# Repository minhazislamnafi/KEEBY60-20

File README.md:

# KEEBY60+20

A moduler 60% mechanical hot-swapble keyboard. With 20% numpad attachment, it will form a proper 80% keyboard.

# Specification

## KEEBY60
* Firmware: QMK
* Layout: Default 60% (main Keyboard)
* Socket: Hot-swapable Kailh Socket
* Switches: Cherry MX blue
* ARGB led: SK6812 mini-E
* MCU: Raspberry Pi RP2040 QFN-56
* USB hub IC: Fe1.1s SSOP-28
* USB IN: 2 type-C (One for USB+Power & another for only power)
* USB OUT: 1 6p magnetic connector & 2 type-c usb 2.0
        
     (2 USB 2.0 is only accessible when only 60% is used)
* Total keys: 63 ANSI layout
* Knob: EC11E rotary encoder (with push switch)
* Diaplay: SSD1306 0.91" I2C Oled 
* PCB: 2-layer (all components bottom mounted)
* Dimensions: pcb - 291* 116 mm (L * W)                                                                        
              case - 304* 130*45 mm  (L * W * H)

## KEEBY20
* firmware: QMK
* Layout: ISO 20% (numpad)
* Socket: Hot-swapable Kailh Socket
* Switches: Cherry MX blue
* ARGB led: SK6812 mini-E
* MCU: Raspberry Pi RP2040 QFN-56
* USB IN: 6p magnetic connector & 1 type-C

     (Both the 6p conn and type-C connector's data pin are connected)
* Total keys: 17 ANSI Numpad
* Knob: EC11E rotary encoder (with push switch)
* Diaplay: SSD1306 0.91" I2C Oled 
* PCB: 2-layer (all components bottom mounted)
* Dimensions: pcb - 81* 116 mm (L * W)                                                                         
              case - 95* 130*45 mm (L * W * H)

# Ask Why KEEBY60+20?

It's a freaking 80% moduler usb2.0 hub, mechanical hot-swappable programmable ARGB LED DIY 3D printed Keyboard with dual knob dual OLED display. wants to know more? It can be used as a single 60% ANSI with 2 USB 2.0 HUB or, a single 17-key numpad macropad or or or as said, a 6-pin magnetic-connected ISO 80% Keyboard. 

TL;DR - The KEEBY60+20 is an all-around very versatile keyboard that runs on open-source QMK firmware.

## Onshape Full assembly [Link](https://cad.onshape.com/documents/68f2d0f77eb15a6c900279e4/w/64c05305f9ae419810eaa342/e/0ee3c387e4a094a987680ffc?renderMode=0&uiState=6a25de67f901e47d9e05b22d)

## CAD Render

## Schematics

## PCB Render
My PC can't handle KiCad 10.0 now. so no render ;(
But I have some screenshots.

## FOLLOW THESE STEPS FOR BUILDING ##

**1. Spend some money $$ to buy the parts mentioned in [BOM](https://github.com/minhazislamnafi/KEEBY60-20/tree/main/PCB/production).**(2 separate BOM)

**2. Order the PCB for KEEBY60 and KEEBY20 using this [GERBER file](https://github.com/minhazislamnafi/KEEBY60-20/blob/main/PCB/production/keeby60/KEEBY_60_v1.1.zip) and [GERBER file](https://github.com/minhazislamnafi/KEEBY60-20/blob/main/PCB/production/keeby20/KEEBY_20_v1.1.zip).**

**3. Solder the SMD components of the PCB by hand ;) Or just order the PCBs with PCBA services, btw it will cost a lot.**

**4. Check with a multimeter: Is the MCU getting 3.3v or not? If not, diagnose by yourself :)**

**5. Place all the key switches.**

**6. Flash QMK firmware using USB connection ( I will add every step in details, once I have built IRL:)**

**7. 3D print the [Case](https://github.com/minhazislamnafi/KEEBY60-20/tree/main/CAD/CASE%203D%20file) .**

**8. Assemble your KEEBY60 and 20.**

**5. Test and enjoy more RGB= more FPS keyboard ( I will add every step in details, once I have built IRL:).**

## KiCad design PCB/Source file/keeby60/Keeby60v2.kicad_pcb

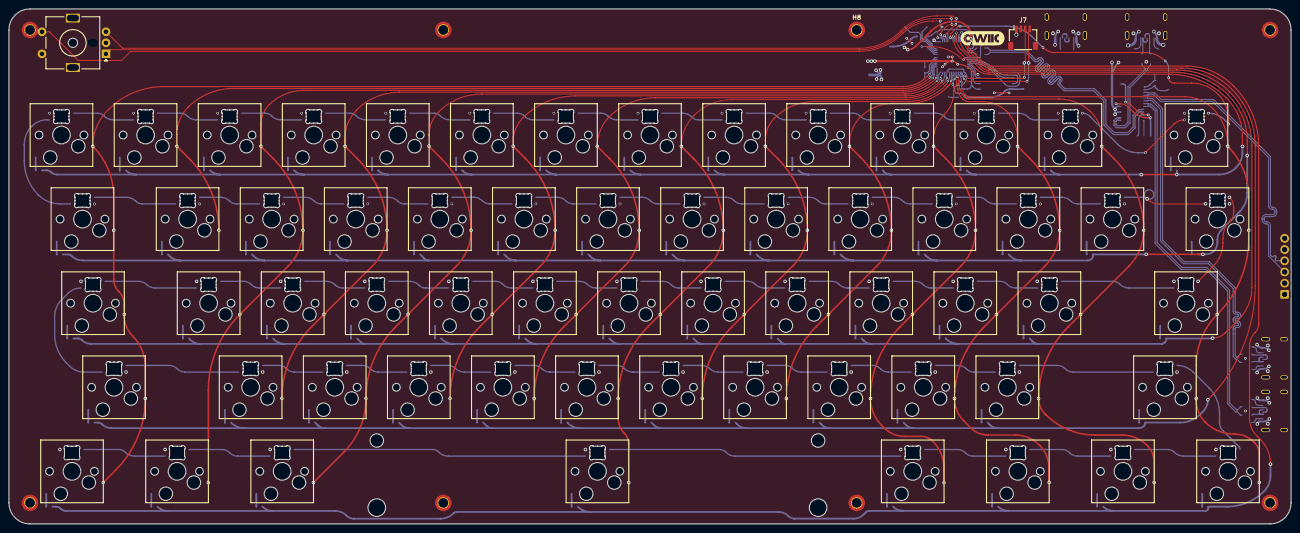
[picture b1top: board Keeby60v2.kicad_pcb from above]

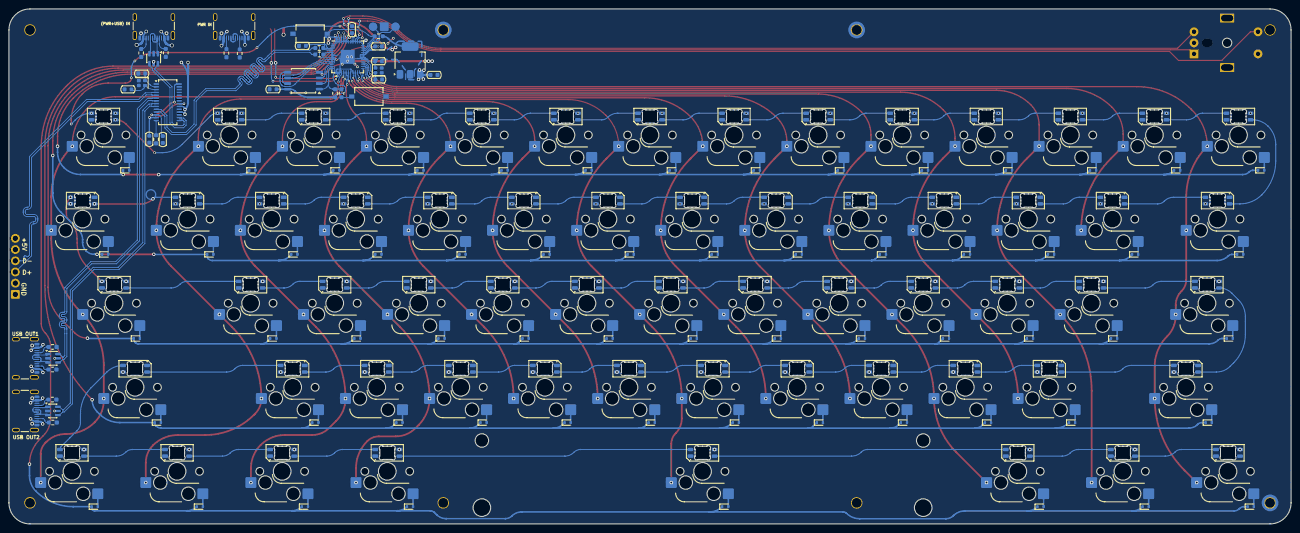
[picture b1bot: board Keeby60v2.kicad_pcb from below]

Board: 2 copper layers, 290.5 x 116.7 mm, 235 parts (163 on the bottom side), 195 nets.

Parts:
C7, C8, C14, C15: 10uF; C_0603_1608Metric
C9, C10: 27pF; C_0603_1608Metric
C11: 0.1uF; C_0603_1608Metric
C12: 100NF; C_0603_1608Metric
C13: 2.2uF; C_0603_1608Metric
C16, C17: 22pF; C_0603_1608Metric
D1, D2, D3, D4, D5, D6, D7, D8, D9, D10, D11, D12, D13, D14, D15, D16, D17, D18, D19, D20, D21, D22, D23, D24, D25, D26, D27, D28, D29, D30, D31, D32, D33, D34, D35, D36, D37, D38, D39, D40, D41, D42, D43, D44, D45, D46, D47, D48, D49, D50, D51, D52, D53, D54, D55, D56, D57, D58, D59, D60, D61: 1N4148WT; D_SOD-523
H1, H7, H8: MountingHole_Pad; MountingHole_2.2mm_M2_DIN965_Pad_TopBottom
H2, H3, H4, H5, H6: MountingHole_Pad; MountingHole_2.2mm_M2_DIN965_Pad_TopOnly
J1, J2, J3, J4: USB_C_Receptacle_USB2.0_16P; USB_C_Receptacle_GCT_USB4105-xx-A_16P_TopMnt_Horizontal
J5: 6P magnetic connecter; TerminalBlock_Xinya_XY308-2.54-6P_1x06_P2.54mm_Horizontal
J6: DEBUG PIN; TerminalBlock_Xinya_XY308-2.54-3P_1x03_P2.54mm_Horizontal
J7: Conn_01x05_Pin; JST_SH_SM04B-SRSS-TB_1x04-1MP_P1.00mm_Horizontal
L1, L2, L3, L4, L5, L6, L7, L8, L9, L10, L11, L12, L13, L14, L15, L16, L17, L18, L19, L20, L21, L22, L23, L24, L25, L26, L27, L28, L29, L30, L31, L32, L33, L34, L35, L36, L37, L38, L39, L40, L41, L42, L43, L44, L45, L46, L47, L48, L49, L50, L51, L52, L53, L54, L55, L56, L57, L58, L59, L60, L61: SK6812MINI-E; LED_SK6812MINI-E_3.2x2.8mm_P1.5mm_ReverseMount
R1, R2, R3, R4, R5, R6, R7, R8: 5.1K; R_0603_1608Metric_Pad0.98x0.95mm_HandSolder
R9, R10: 27R; R_0603_1608Metric_Pad0.98x0.95mm_HandSolder
R11: 1K; R_0603_1608Metric_Pad0.98x0.95mm_HandSolder
R12, R13: 10K; R_0603_1608Metric_Pad0.98x0.95mm_HandSolder
R14: 12K; R_0603_1608Metric_Pad0.98x0.95mm_HandSolder
SW1, SW2, SW3, SW4, SW5, SW6, SW7, SW8, SW9, SW10, SW11, SW12, SW13, SW16, SW17, SW18, SW19, SW20, SW21, SW22, SW23, SW24, SW25, SW26, SW27, SW30, SW31, SW32, SW33, SW34, SW35, SW36, SW37, SW38, SW39, SW40, SW43, SW44, SW45, SW46, SW47, SW48, SW49, SW50, SW51, SW52: SW_Push; SW_Hotswap_Kailh_MX_1.00u
SW14: SW_Push; SW_Hotswap_Kailh_MX_2.00u
SW15, SW28: SW_Push; SW_Hotswap_Kailh_MX_1.50u
SW29: SW_Push; SW_Hotswap_Kailh_MX_1.75u
SW41, SW42: SW_Push; SW_Hotswap_Kailh_MX_2.25u
SW53: SW_Push; SW_Hotswap_Kailh_MX_2.75u
SW54, SW55, SW56, SW58, SW59, SW60, SW61: SW_Push; SW_Hotswap_Kailh_MX_1.25u
SW57: SW_Push; SW_Hotswap_Kailh_MX_6.25u
SW62: RotaryEncoder_Switch_MP; RotaryEncoder_Alps_EC11E-Switch_Vertical_H20mm_MountingHoles
SW63, SW64: SW_Push; SW_Tactile_SPST_NO_Straight_CK_PTS636Sx25SMTRLFS
U4: RP2040; QFN-56-1EP_7x7mm_P0.4mm_EP3.2x3.2mm
U5: AMS1117-3.3; SOT-223-3_TabPin2
U6: W25Q128JVS; SOIC-8_5.3x5.3mm_P1.27mm
U7: FE1.1s; SSOP-28_3.9x9.9mm_P0.635mm
U8, U9, U10: USBLC6-2SC6; SOT-23-6
Y2, Y3: 12MHz; Crystal_SMD_2016-4Pin_2.0x1.6mm

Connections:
+5V: C7.1, J1.A4 (VBUS), J1.A9 (VBUS), J1.B4 (VBUS), J1.B9 (VBUS), J2.A4 (VBUS), J2.A9 (VBUS), J2.B4 (VBUS), J2.B9 (VBUS), J3.A4 (VBUS), J3.A9 (VBUS), J3.B4 (VBUS), J3.B9 (VBUS), J4.A4 (VBUS), J4.A9 (VBUS), J4.B4 (VBUS), J4.B9 (VBUS), J5.5, J5.6, J7.2, L1.3 (VDD), L2.3 (VDD), L3.3 (VDD), L4.3 (VDD), L5.3 (VDD), L6.3 (VDD), L7.3 (VDD), L8.3 (VDD), L9.3 (VDD), L10.3 (VDD), L11.3 (VDD), L12.3 (VDD), L13.3 (VDD), L14.3 (VDD), L15.3 (VDD), L16.3 (VDD), L17.3 (VDD), L18.3 (VDD), L19.3 (VDD), L20.3 (VDD), L21.3 (VDD), L22.3 (VDD), L23.3 (VDD), L24.3 (VDD), L25.3 (VDD), L26.3 (VDD), L27.3 (VDD), L28.3 (VDD), L29.3 (VDD), L30.3 (VDD), L31.3 (VDD), L32.3 (VDD), L33.3 (VDD), L34.3 (VDD), L35.3 (VDD), L36.3 (VDD), L37.3 (VDD), L38.3 (VDD), L39.3 (VDD), L40.3 (VDD), L41.3 (VDD), L42.3 (VDD), L43.3 (VDD), L44.3 (VDD), L45.3 (VDD), L46.3 (VDD), L47.3 (VDD), L48.3 (VDD), L49.3 (VDD), L50.3 (VDD), L51.3 (VDD), L52.3 (VDD), L53.3 (VDD), L54.3 (VDD), L55.3 (VDD), L56.3 (VDD), L57.3 (VDD), L58.3 (VDD), L59.3 (VDD), L60.3 (VDD), L61.3 (VDD), U5.3 (VI), U7.18 (VBUSM), U7.20 (VDD5), U8.5 (VBUS), U9.5 (VBUS), U10.5 (VBUS)
COL1: SW1.1, SW15.1, SW29.1, SW42.1, SW54.1, U4.18 (GPIO15)
COL2: SW2.1, SW16.1, U4.17 (GPIO14)
COL3: SW3.1, SW17.1, SW30.1, SW55.1, U4.16 (GPIO13)
COL4: SW4.1, SW18.1, SW31.1, SW43.1, U4.15 (GPIO12)
COL5: SW5.1, SW19.1, SW32.1, SW44.1, SW56.1, U4.14 (GPIO11)
COL6: SW6.1, SW20.1, SW33.1, SW45.1, U4.13 (GPIO10)
COL7: SW7.1, SW21.1, SW34.1, SW46.1, U4.12 (GPIO9)
COL8: SW8.1, SW22.1, SW35.1, SW47.1, SW57.1, U4.11 (GPIO8)
COL9: SW9.1, SW23.1, SW36.1, SW48.1, U4.9 (GPIO7)
COL10: SW10.1, SW24.1, SW37.1, SW49.1, U4.8 (GPIO6)
COL11: SW11.1, SW25.1, SW38.1, SW50.1, SW58.1, U4.7 (GPIO5)
COL12: SW12.1, SW26.1, SW39.1, SW51.1, SW59.1, U4.6 (GPIO4)
COL13: SW13.1, SW27.1, SW40.1, SW52.1, SW60.1, U4.5 (GPIO3)
COL14: SW14.1, SW28.1, SW41.1, SW53.1, SW61.1, U4.4 (GPIO2)
CS: R11.1, R12.2, U4.56 (~QSPI_SS), U6.1 (~CS)
DIN: L14.2 (DIN), U4.36 (GPIO24)
GND: C7.2, C8.2, C9.2, C10.1, C11.1, C12.1, C13.2, C14.1, C15.1, C16.1, C17.2, H1.1 (1_1), H2.1 (1_1), H3.1 (1_1), H5.1 (1_1), H6.1 (1_1), H7.1 (1_1), H8.1 (1_1), J1.A1 (GND), J1.A12 (GND), J1.B1 (GND), J1.B12 (GND), J1.SH (SHIELD), J2.A1 (GND), J2.A12 (GND), J2.B1 (GND), J2.B12 (GND), J2.SH (SHIELD), J3.A1 (GND), J3.A12 (GND), J3.B1 (GND), J3.B12 (GND), J3.SH (SHIELD), J4.A1 (GND), J4.A12 (GND), J4.B1 (GND), J4.B12 (GND), J4.SH (SHIELD), J5.1, J5.2, J6.2, J7.1, L1.1 (VSS), L2.1 (VSS), L3.1 (VSS), L4.1 (VSS), L5.1 (VSS), L6.1 (VSS), L7.1 (VSS), L8.1 (VSS), L9.1 (VSS), L10.1 (VSS), L11.1 (VSS), L12.1 (VSS), L13.1 (VSS), L14.1 (VSS), L15.1 (VSS), L16.1 (VSS), L17.1 (VSS), L18.1 (VSS), L19.1 (VSS), L20.1 (VSS), L21.1 (VSS), L22.1 (VSS), L23.1 (VSS), L24.1 (VSS), L25.1 (VSS), L26.1 (VSS), L27.1 (VSS), L28.1 (VSS), L29.1 (VSS), L30.1 (VSS), L31.1 (VSS), L32.1 (VSS), L33.1 (VSS), L34.1 (VSS), L35.1 (VSS), L36.1 (VSS), L37.1 (VSS), L38.1 (VSS), L39.1 (VSS), L40.1 (VSS), L41.1 (VSS), L42.1 (VSS), L43.1 (VSS), L44.1 (VSS), L45.1 (VSS), L46.1 (VSS), L47.1 (VSS), L48.1 (VSS), L49.1 (VSS), L50.1 (VSS), L51.1 (VSS), L52.1 (VSS), L53.1 (VSS), L54.1 (VSS), L55.1 (VSS), L56.1 (VSS), L57.1 (VSS), L58.1 (VSS), L59.1 (VSS), L60.1 (VSS), L61.1 (VSS), R1.2, R2.2, R3.2, R4.2, R5.2, R6.2, R7.2, R8.2, R14.1, SW62.C, SW62.MP, SW62.S2, SW63.2, SW64.1, U4.19 (TESTEN), U4.57 (GND), U5.1 (GND), U6.4 (GND), U7.1 (VSS), U7.27 (TESTJ/EESDA), U8.2 (GND), U9.2 (GND), U10.2 (GND), Y2.2 (G), Y2.3 (G), Y3.2 (G), Y3.3 (G)
MAG_D+: J5.3, U7.5 (DP4)
MAG_D-: J5.4, U7.4 (DM4)
MCU3.3V: C8.1, C11.2, R12.1, R13.2, U4.1 (IOVDD), U4.10 (IOVDD), U4.22 (IOVDD), U4.33 (IOVDD), U4.42 (IOVDD), U4.43 (ADC_AVDD), U4.44 (VREG_VIN), U4.48 (USB_VDD), U4.49 (IOVDD), U5.2 (VO), U6.8 (VCC)
MCU_D+: R9.1, U7.10 (DM1)
MCU_D-: R10.1, U7.11 (DP1)
unnamed: D1.2 (A), SW1.2
unnamed: D2.2 (A), SW2.2
unnamed: D3.2 (A), SW3.2
unnamed: D4.2 (A), SW4.2
unnamed: D5.2 (A), SW5.2
unnamed: D6.2 (A), SW6.2
unnamed: D7.2 (A), SW7.2
unnamed: D8.2 (A), SW8.2
unnamed: D9.2 (A), SW9.2
unnamed: D10.2 (A), SW10.2
unnamed: D11.2 (A), SW11.2
unnamed: D12.2 (A), SW12.2
unnamed: D13.2 (A), SW13.2
unnamed: D14.2 (A), SW14.2
unnamed: D15.2 (A), SW15.2
unnamed: D16.2 (A), SW16.2
unnamed: D17.2 (A), SW17.2
unnamed: D18.2 (A), SW18.2
unnamed: D19.2 (A), SW19.2
unnamed: D20.2 (A), SW20.2
unnamed: D21.2 (A), SW21.2
unnamed: D22.2 (A), SW22.2
unnamed: D23.2 (A), SW23.2
unnamed: D24.2 (A), SW24.2
unnamed: D25.2 (A), SW25.2
unnamed: D26.2 (A), SW26.2
unnamed: D27.2 (A), SW27.2
unnamed: D28.2 (A), SW28.2
unnamed: D29.2 (A), SW29.2
unnamed: D30.2 (A), SW30.2
unnamed: D31.2 (A), SW31.2
unnamed: D32.2 (A), SW32.2
unnamed: D33.2 (A), SW33.2
unnamed: D34.2 (A), SW34.2
unnamed: D35.2 (A), SW35.2
unnamed: D36.2 (A), SW36.2
unnamed: D37.2 (A), SW37.2
unnamed: D38.2 (A), SW38.2
unnamed: D39.2 (A), SW39.2
unnamed: D40.2 (A), SW40.2
unnamed: D41.2 (A), SW41.2
unnamed: D42.2 (A), SW42.2
unnamed: D43.2 (A), SW43.2
unnamed: D44.2 (A), SW44.2
unnamed: D45.2 (A), SW45.2
unnamed: D46.2 (A), SW46.2
unnamed: D47.2 (A), SW47.2
unnamed: D48.2 (A), SW48.2
unnamed: D49.2 (A), SW49.2
unnamed: D50.2 (A), SW50.2
unnamed: D51.2 (A), SW51.2
unnamed: D52.2 (A), SW52.2
unnamed: D53.2 (A), SW53.2
unnamed: D54.2 (A), SW54.2
unnamed: D55.2 (A), SW55.2
unnamed: D56.2 (A), SW56.2
unnamed: D57.2 (A), SW57.2
unnamed: D58.2 (A), SW58.2
unnamed: D59.2 (A), SW59.2
unnamed: D60.2 (A), SW60.2
unnamed: D61.2 (A), SW61.2
unnamed: J1.A5 (CC1), R5.1
unnamed: J1.B5 (CC2), R6.1
unnamed: J1.A6 (D+), J1.B6 (D+), U8.3 (I/O2)
unnamed: J1.A7 (D-), J1.B7 (D-), U8.1 (I/O1)
unnamed: J2.A5 (CC1), R1.1
unnamed: J2.B5 (CC2), R2.1
unnamed: J2.A6 (D+), J2.B6 (D+), U9.3 (I/O2)
unnamed: J2.A7 (D-), J2.B7 (D-), U9.1 (I/O1)
unnamed: J3.A5 (CC1), R3.1
unnamed: J3.B5 (CC2), R4.1
unnamed: J3.A6 (D+), J3.B6 (D+), U10.3 (I/O2)
unnamed: J3.A7 (D-), J3.B7 (D-), U10.1 (I/O1)
unnamed: J4.A5 (CC1), R7.1
unnamed: J4.B5 (CC2), R8.1
unnamed: J4.A6 (D+), J4.B6 (D+)
unnamed: J4.A7 (D-), J4.B7 (D-)
unnamed: L1.2 (DIN), L2.4 (DOUT)
unnamed: L1.4 (DOUT), L15.2 (DIN)
unnamed: L2.2 (DIN), L3.4 (DOUT)
unnamed: L3.2 (DIN), L4.4 (DOUT)
unnamed: L4.2 (DIN), L5.4 (DOUT)
unnamed: L5.2 (DIN), L6.4 (DOUT)
unnamed: L6.2 (DIN), L7.4 (DOUT)
unnamed: L7.2 (DIN), L8.4 (DOUT)
unnamed: L8.2 (DIN), L9.4 (DOUT)
unnamed: L10.2 (DIN), L11.4 (DOUT)
unnamed: L9.2 (DIN), L10.4 (DOUT)
unnamed: L11.2 (DIN), L12.4 (DOUT)
unnamed: L12.2 (DIN), L13.4 (DOUT)
unnamed: L13.2 (DIN), L14.4 (DOUT)
unnamed: L15.4 (DOUT), L16.2 (DIN)
unnamed: L16.4 (DOUT), L17.2 (DIN)
unnamed: L17.4 (DOUT), L18.2 (DIN)
unnamed: L18.4 (DOUT), L19.2 (DIN)
unnamed: L19.4 (DOUT), L20.2 (DIN)
unnamed: L20.4 (DOUT), L21.2 (DIN)
unnamed: L21.4 (DOUT), L22.2 (DIN)
unnamed: L22.4 (DOUT), L23.2 (DIN)
unnamed: L23.4 (DOUT), L24.2 (DIN)
unnamed: L24.4 (DOUT), L25.2 (DIN)
unnamed: L25.4 (DOUT), L26.2 (DIN)
unnamed: L26.4 (DOUT), L27.2 (DIN)
unnamed: L27.4 (DOUT), L28.2 (DIN)
unnamed: L28.4 (DOUT), L41.2 (DIN)
unnamed: L29.2 (DIN), L30.4 (DOUT)
unnamed: L29.4 (DOUT), L42.2 (DIN)
unnamed: L30.2 (DIN), L31.4 (DOUT)
unnamed: L31.2 (DIN), L32.4 (DOUT)
unnamed: L32.2 (DIN), L33.4 (DOUT)
unnamed: L33.2 (DIN), L34.4 (DOUT)
unnamed: L34.2 (DIN), L35.4 (DOUT)
unnamed: L35.2 (DIN), L36.4 (DOUT)
unnamed: L36.2 (DIN), L37.4 (DOUT)
unnamed: L37.2 (DIN), L38.4 (DOUT)
unnamed: L38.2 (DIN), L39.4 (DOUT)
unnamed: L39.2 (DIN), L40.4 (DOUT)
unnamed: L40.2 (DIN), L41.4 (DOUT)
unnamed: L42.4 (DOUT), L43.2 (DIN)
unnamed: L43.4 (DOUT), L44.2 (DIN)
unnamed: L44.4 (DOUT), L45.2 (DIN)
unnamed: L45.4 (DOUT), L46.2 (DIN)
unnamed: L46.4 (DOUT), L47.2 (DIN)
unnamed: L47.4 (DOUT), L48.2 (DIN)
unnamed: L48.4 (DOUT), L49.2 (DIN)
unnamed: L49.4 (DOUT), L50.2 (DIN)
unnamed: L50.4 (DOUT), L51.2 (DIN)
unnamed: L51.4 (DOUT), L52.2 (DIN)
unnamed: L52.4 (DOUT), L53.2 (DIN)
unnamed: L53.4 (DOUT), L61.2 (DIN)
unnamed: L54.2 (DIN), L55.4 (DOUT)
unnamed: L55.2 (DIN), L56.4 (DOUT)
unnamed: L56.2 (DIN), L57.4 (DOUT)
unnamed: L57.2 (DIN), L58.4 (DOUT)
unnamed: L58.2 (DIN), L59.4 (DOUT)
unnamed: L59.2 (DIN), L60.4 (DOUT)
unnamed: L60.2 (DIN), L61.4 (DOUT)
unnamed: R11.2, SW63.1
unnamed: U4.52 (QSPI_SCLK), U6.6 (CLK)
unnamed: U4.53 (QSPI_SD0), U6.5 (DI/IO_{0})
unnamed: U4.55 (QSPI_SD1), U6.2 (DO/IO_{1})
unnamed: U4.54 (QSPI_SD2), U6.3 (~WP/IO_{2})
unnamed: U4.51 (QSPI_SD3), U6.7 (~HOLD/~RESET/IO_{3})
unnamed: R13.1, SW64.2, U4.26 (RUN)
unnamed: R9.2, U4.46 (USB_DM)
unnamed: R10.2, U4.47 (USB_DP)
unnamed: C12.2, C13.1, U4.23 (DVDD), U4.45 (VREG_VOUT), U4.50 (DVDD)
unnamed: C9.1, U4.20 (XIN), Y2.1
unnamed: C10.2, U4.21 (XOUT), Y2.4
unnamed: R14.2, U7.14 (REXT)
unnamed: C15.2, U7.12 (VD18_O), U7.28 (VD18)
unnamed: C14.2, U7.13 (VD33), U7.21 (VD33_O)
unnamed: C17.1, U7.3 (XIN), Y3.4
unnamed: C16.2, U7.2 (XOUT), Y3.1
OUTA: SW62.A, U4.31 (GPIO20)
OUTB: SW62.B, U4.32 (GPIO21)
ROW1: D1.1 (K), D2.1 (K), D3.1 (K), D4.1 (K), D5.1 (K), D6.1 (K), D7.1 (K), D8.1 (K), D9.1 (K), D10.1 (K), D11.1 (K), D12.1 (K), D13.1 (K), D14.1 (K), U4.37 (GPIO25)
ROW2: D15.1 (K), D16.1 (K), D17.1 (K), D18.1 (K), D19.1 (K), D20.1 (K), D21.1 (K), D22.1 (K), D23.1 (K), D24.1 (K), D25.1 (K), D26.1 (K), D27.1 (K), D28.1 (K), U4.38 (GPIO26/ADC0)
ROW3: D29.1 (K), D30.1 (K), D31.1 (K), D32.1 (K), D33.1 (K), D34.1 (K), D35.1 (K), D36.1 (K), D37.1 (K), D38.1 (K), D39.1 (K), D40.1 (K), D41.1 (K), U4.39 (GPIO27/ADC1)
ROW4: D42.1 (K), D43.1 (K), D44.1 (K), D45.1 (K), D46.1 (K), D47.1 (K), D48.1 (K), D49.1 (K), D50.1 (K), D51.1 (K), D52.1 (K), D53.1 (K), U4.40 (GPIO28/ADC2)
ROW5: D54.1 (K), D55.1 (K), D56.1 (K), D57.1 (K), D58.1 (K), D59.1 (K), D60.1 (K), D61.1 (K), U4.41 (GPIO29/ADC3)
SCL: J7.4, U4.3 (GPIO1)
SCLK: J6.1, U4.24 (SWCLK)
SDA: J7.3, U4.2 (GPIO0)
SDIO: J6.3, U4.25 (SWDIO)
SW: H4.1 (1_1), SW62.S1, U4.30 (GPIO19)
USBD1D+: U7.9 (DP2), U9.4 (I/O2)
USBD1D-: U7.8 (DM2), U9.6 (I/O1)
USBD2D+: U7.7 (DP3), U10.4 (I/O2)
USBD2D-: U7.6 (DM3), U10.6 (I/O1)
USBUD+: U7.16 (DPU), U8.4 (I/O2)
USBUD-: U7.15 (DMU), U8.6 (I/O1)

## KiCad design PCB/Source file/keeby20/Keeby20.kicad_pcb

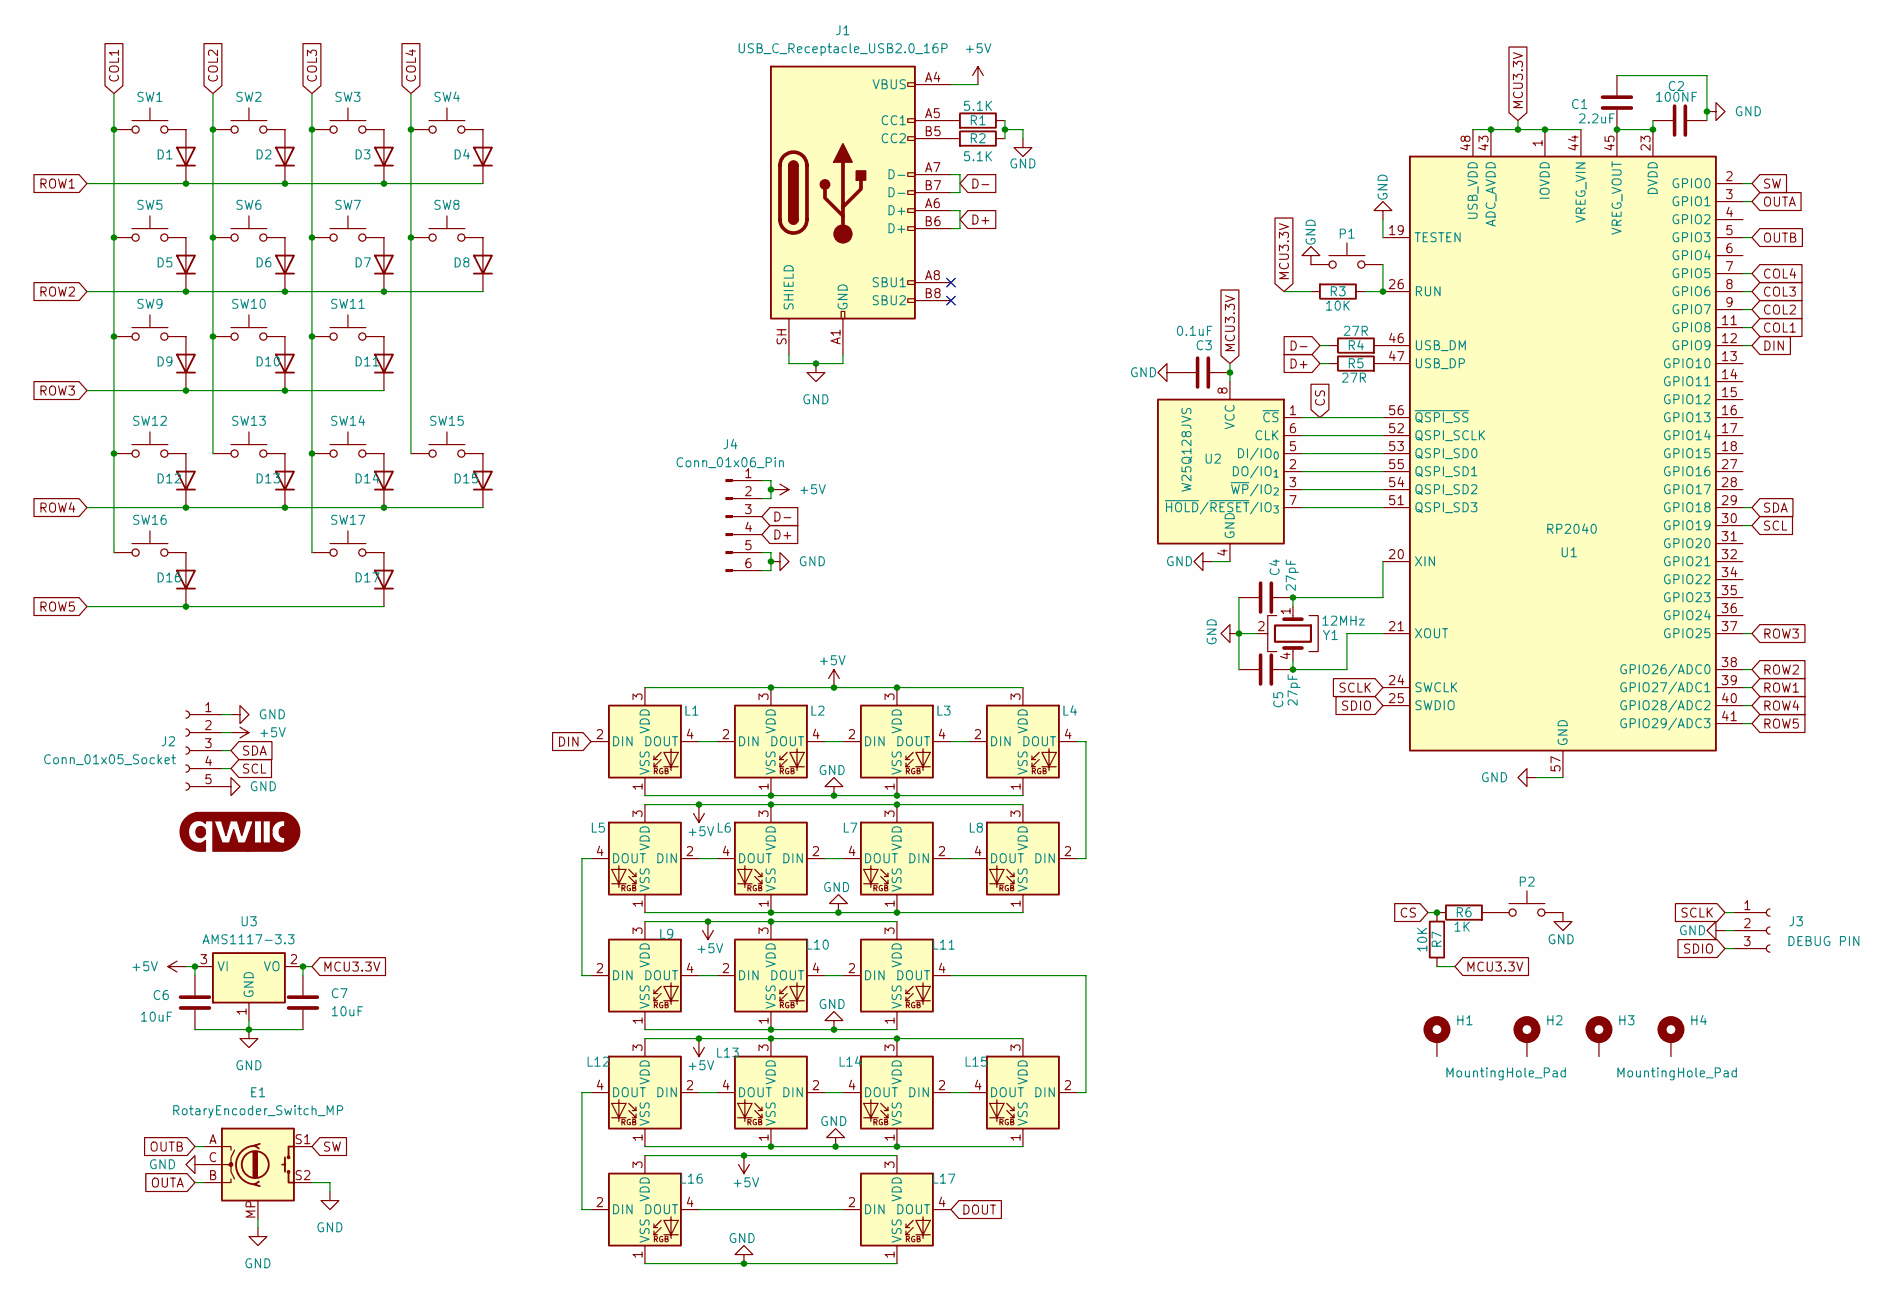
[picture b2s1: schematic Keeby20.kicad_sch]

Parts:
C1: 2.2uF; C_0603_1608Metric
C2: 100NF; C_0603_1608Metric
C3: 0.1uF; C_0603_1608Metric
C4, C5: 27pF; C_0603_1608Metric
C6, C7: 10uF; C_0603_1608Metric
D1, D2, D3, D4, D5, D6, D7, D8, D9, D10, D11, D12, D13, D14, D15, D16, D17: 1N4148WT; D_SOD-523
E1: RotaryEncoder_Switch_MP; RotaryEncoder_Alps_EC11E-Switch_Vertical_H20mm_MountingHoles
G1: qwiic_Logo
H1, H2, H3, H4: MountingHole_Pad; MountingHole_2.2mm_M2_Pad
J1: USB_C_Receptacle_USB2.0_16P; USB_C_Receptacle_GCT_USB4105-xx-A_16P_TopMnt_Horizontal
J2: Conn_01x05_Socket; JST_SH_SM04B-SRSS-TB_1x04-1MP_P1.00mm_Horizontal
J3: DEBUG PIN; TerminalBlock_Xinya_XY308-2.54-3P_1x03_P2.54mm_Horizontal
J4: Conn_01x06_Pin; PinHeader_1x06_P2.54mm_Vertical
L1, L2, L3, L4, L5, L6, L7, L8, L9, L10, L11, L12, L13, L14, L15, L16, L17: SK6812MINI-E; LED_SK6812MINI-E_3.2x2.8mm_P1.5mm_ReverseMount
P1, P2: SW_Push; SW_SPST_CK_KXT3
R1, R2: 5.1K; R_0603_1608Metric
R3, R7: 10K; R_0603_1608Metric_Pad0.98x0.95mm_HandSolder
R4, R5: 27R; R_0603_1608Metric_Pad0.98x0.95mm_HandSolder
R6: 1K; R_0603_1608Metric_Pad0.98x0.95mm_HandSolder
SW1, SW2, SW3, SW4, SW5, SW6, SW7, SW9, SW10, SW11, SW12, SW13, SW14, SW17: SW_Push; SW_Hotswap_Kailh_MX_1.00u
SW8, SW15: SW_Push; SW_Hotswap_Kailh_MX_2.00u_90deg
SW16: SW_Push; SW_Hotswap_Kailh_MX_2.00u
U1: RP2040; QFN-56-1EP_7x7mm_P0.4mm_EP3.2x3.2mm
U2: W25Q128JVS; SOIC-8_5.3x5.3mm_P1.27mm
U3: AMS1117-3.3; SOT-223-3_TabPin2
Y1: 12MHz; Crystal_SMD_2016-4Pin_2.0x1.6mm

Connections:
+5V: C6.1, J1.A4 (VBUS), J1.A9 (VBUS), J1.B4 (VBUS), J1.B9 (VBUS), J2.2, J4.1, J4.2, L1.3 (VDD), L2.3 (VDD), L3.3 (VDD), L4.3 (VDD), L5.3 (VDD), L6.3 (VDD), L7.3 (VDD), L8.3 (VDD), L9.3 (VDD), L10.3 (VDD), L11.3 (VDD), L12.3 (VDD), L13.3 (VDD), L14.3 (VDD), L15.3 (VDD), L16.3 (VDD), L17.3 (VDD), U3.3 (VI)
COL1: SW1.1, SW5.1, SW9.1, SW12.1, SW16.1, U1.11 (GPIO8)
COL2: SW2.1, SW6.1, SW10.1, SW13.1, U1.9 (GPIO7)
COL3: SW3.1, SW7.1, SW11.1, SW14.1, SW17.1, U1.8 (GPIO6)
COL4: SW4.1, SW8.1, SW15.1, U1.7 (GPIO5)
CS: R6.1, R7.2, U1.56 (~QSPI_SS), U2.1 (~CS)
D+: J1.A6 (D+), J1.B6 (D+), J4.4, R5.1
D-: J1.A7 (D-), J1.B7 (D-), J4.3, R4.1
DIN: L1.2 (DIN), U1.12 (GPIO9)
DOUT: L17.4 (DOUT)
GND: C1.2, C2.1, C3.1, C4.2, C5.1, C6.2, C7.2, E1.C, E1.MP, E1.S2, J1.A1 (GND), J1.A12 (GND), J1.B1 (GND), J1.B12 (GND), J1.SH (SHIELD), J2.1, J2.5, J2.MP, J3.2, J4.5, J4.6, L1.1 (VSS), L2.1 (VSS), L3.1 (VSS), L4.1 (VSS), L5.1 (VSS), L6.1 (VSS), L7.1 (VSS), L8.1 (VSS), L9.1 (VSS), L10.1 (VSS), L11.1 (VSS), L12.1 (VSS), L13.1 (VSS), L14.1 (VSS), L15.1 (VSS), L16.1 (VSS), L17.1 (VSS), P1.1, P2.2, R1.2, R2.2, U1.19 (TESTEN), U1.57 (GND), U2.4 (GND), U3.1 (GND), Y1.2 (G), Y1.3 (G)
MCU3.3V: C3.2, C7.1, R3.2, R7.1, U1.1 (IOVDD), U1.10 (IOVDD), U1.22 (IOVDD), U1.33 (IOVDD), U1.42 (IOVDD), U1.43 (ADC_AVDD), U1.44 (VREG_VIN), U1.48 (USB_VDD), U1.49 (IOVDD), U2.8 (VCC), U3.2 (VO)
unnamed: D1.2 (A), SW1.2
unnamed: D2.2 (A), SW2.2
unnamed: D3.2 (A), SW3.2
unnamed: D4.2 (A), SW4.2
unnamed: D5.2 (A), SW5.2
unnamed: D6.2 (A), SW6.2
unnamed: D7.2 (A), SW7.2
unnamed: D8.2 (A), SW8.2
unnamed: D9.2 (A), SW9.2
unnamed: D10.2 (A), SW10.2
unnamed: D11.2 (A), SW11.2
unnamed: D12.2 (A), SW12.2
unnamed: D13.2 (A), SW13.2
unnamed: D14.2 (A), SW14.2
unnamed: D15.2 (A), SW15.2
unnamed: D16.2 (A), SW16.2
unnamed: D17.2 (A), SW17.2
unnamed: J1.A5 (CC1), R1.1
unnamed: J1.B5 (CC2), R2.1
unnamed: L1.4 (DOUT), L2.2 (DIN)
unnamed: L2.4 (DOUT), L3.2 (DIN)
unnamed: L3.4 (DOUT), L4.2 (DIN)
unnamed: L4.4 (DOUT), L8.2 (DIN)
unnamed: L5.2 (DIN), L6.4 (DOUT)
unnamed: L5.4 (DOUT), L9.2 (DIN)
unnamed: L6.2 (DIN), L7.4 (DOUT)
unnamed: L7.2 (DIN), L8.4 (DOUT)
unnamed: L9.4 (DOUT), L10.2 (DIN)
unnamed: L10.4 (DOUT), L11.2 (DIN)
unnamed: L11.4 (DOUT), L15.2 (DIN)
unnamed: L12.2 (DIN), L13.4 (DOUT)
unnamed: L12.4 (DOUT), L16.2 (DIN)
unnamed: L13.2 (DIN), L14.4 (DOUT)
unnamed: L14.2 (DIN), L15.4 (DOUT)
unnamed: L16.4 (DOUT), L17.2 (DIN)
unnamed: P2.1, R6.2
unnamed: U1.52 (QSPI_SCLK), U2.6 (CLK)
unnamed: U1.53 (QSPI_SD0), U2.5 (DI/IO_{0})
unnamed: U1.55 (QSPI_SD1), U2.2 (DO/IO_{1})
unnamed: U1.54 (QSPI_SD2), U2.3 (~WP/IO_{2})
unnamed: U1.51 (QSPI_SD3), U2.7 (~HOLD/~RESET/IO_{3})
unnamed: P1.2, R3.1, U1.26 (RUN)
unnamed: R4.2, U1.46 (USB_DM)
unnamed: R5.2, U1.47 (USB_DP)
unnamed: C1.1, C2.2, U1.23 (DVDD), U1.45 (VREG_VOUT), U1.50 (DVDD)
unnamed: C4.1, U1.20 (XIN), Y1.1
unnamed: C5.2, U1.21 (XOUT), Y1.4
OUTA: E1.B, U1.3 (GPIO1)
OUTB: E1.A, U1.5 (GPIO3)
ROW1: D1.1 (K), D2.1 (K), D3.1 (K), D4.1 (K), U1.39 (GPIO27/ADC1)
ROW2: D5.1 (K), D6.1 (K), D7.1 (K), D8.1 (K), U1.38 (GPIO26/ADC0)
ROW3: D9.1 (K), D10.1 (K), D11.1 (K), U1.37 (GPIO25)
ROW4: D12.1 (K), D13.1 (K), D14.1 (K), D15.1 (K), U1.40 (GPIO28/ADC2)
ROW5: D16.1 (K), D17.1 (K), U1.41 (GPIO29/ADC3)
SCL: J2.4, U1.30 (GPIO19)
SCLK: J3.1, U1.24 (SWCLK)
SDA: J2.3, U1.29 (GPIO18)
SDIO: J3.3, U1.25 (SWDIO)
SW: E1.S1, U1.2 (GPIO0)

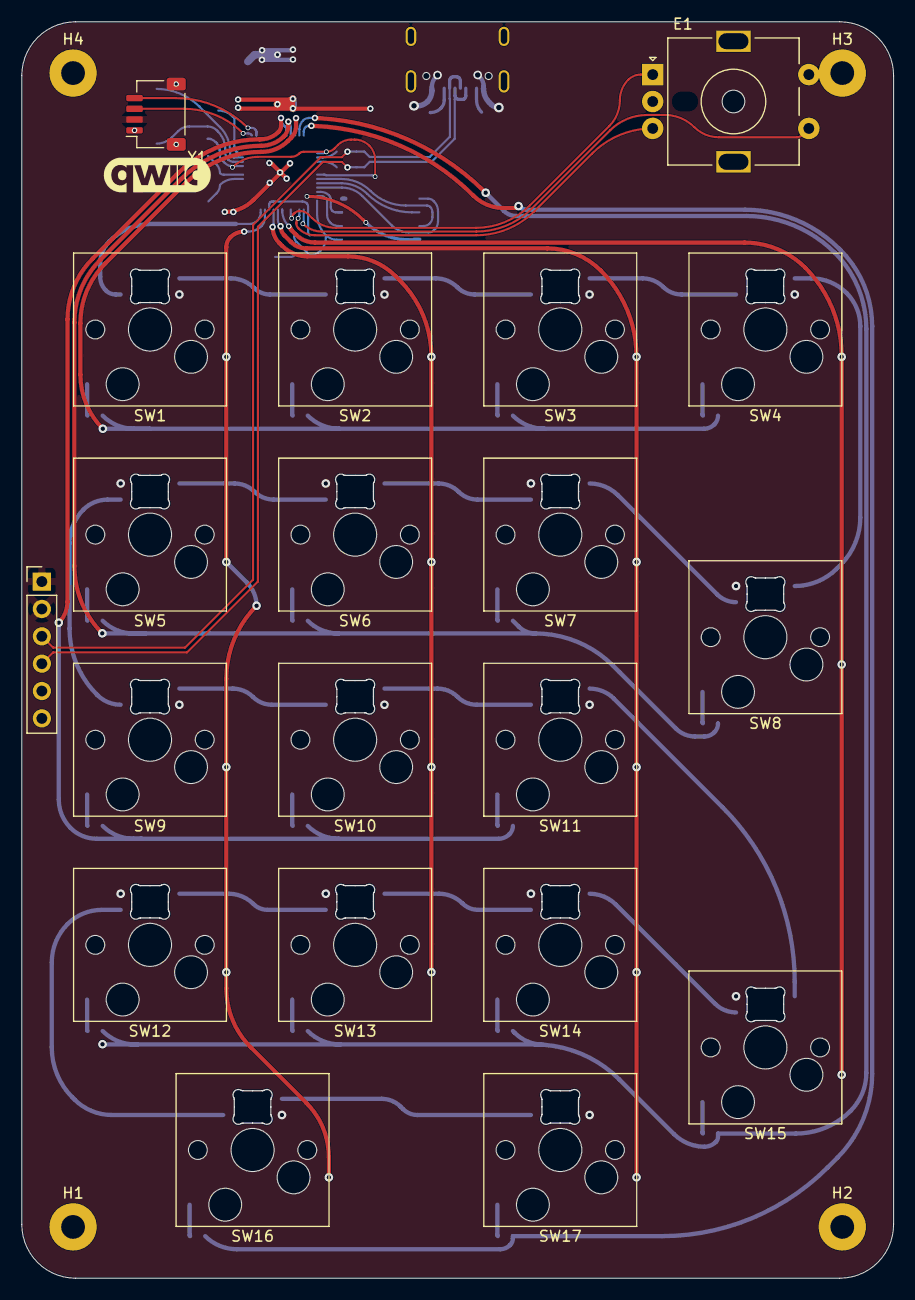
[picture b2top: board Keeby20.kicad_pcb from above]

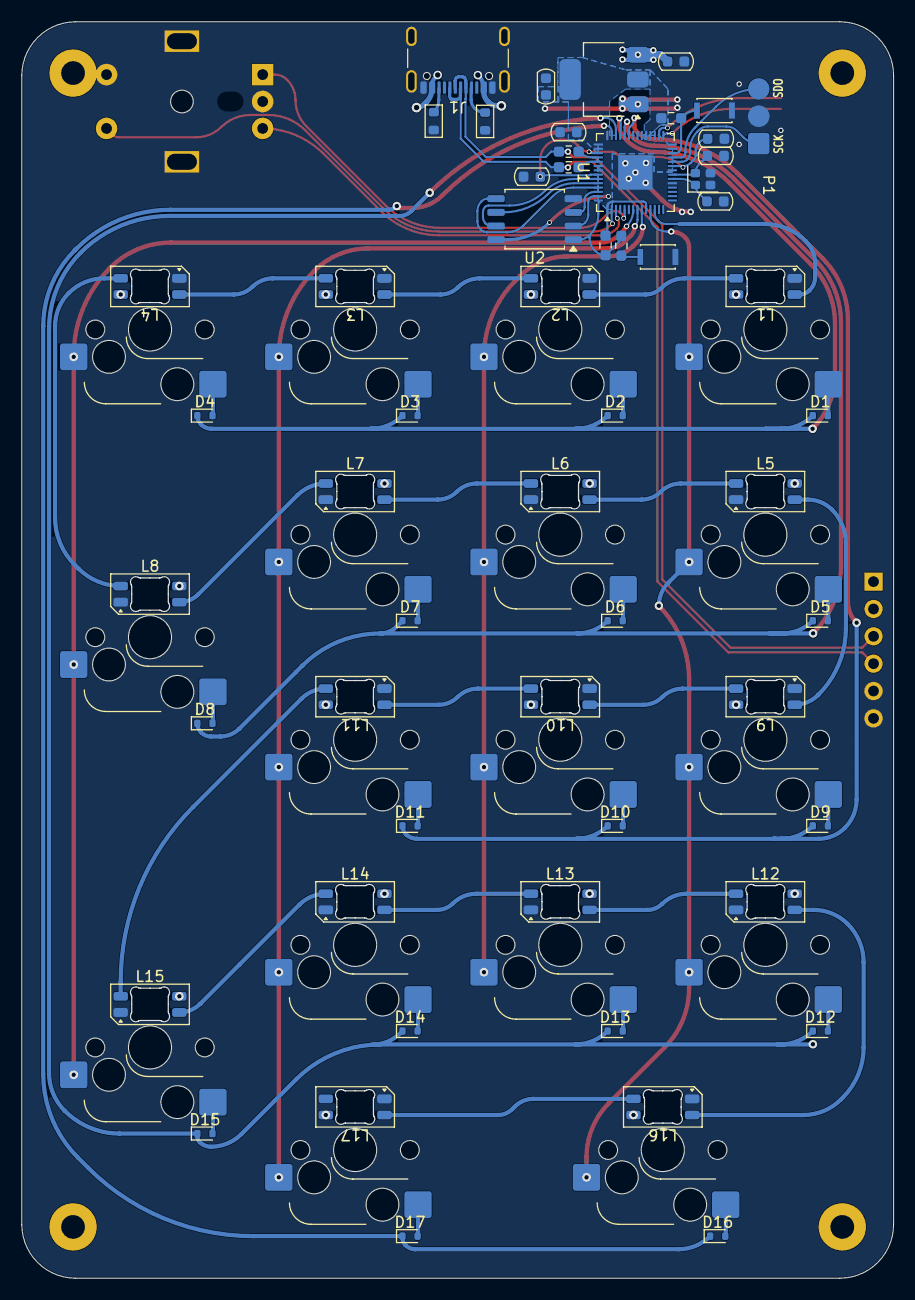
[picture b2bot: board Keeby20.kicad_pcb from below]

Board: 2 copper layers, 81.0 x 116.7 mm, 80 parts (56 on the bottom side), 70 nets.

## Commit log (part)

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2026-06-05 Replace GNU GPL with CERN Open Hardware Licence
2026-06-05 Fix layout badge URL in README.md
2026-06-05 Fix typo in layout badge in README.md
2026-06-06 Create dfg
2026-06-06 Create hs
2026-06-06 Create tehaet
2026-06-06 Create fhbaef
2026-06-06 Create 1
2026-06-06 Create 2
2026-06-06 Create 3
2026-06-06 Create jrsyk
2026-06-06 Add configuration settings for KEEBY20 firmware
2026-06-06 Add rules.mk for KEEBY20 firmware configuration
2026-06-06 Add keyboard configuration for KEEBY60
2026-06-06 Add qmk.json configuration for KEEBY60 firmware
2026-06-06 Update README with device specifications
    Added specifications for total keys, knobs, display, PCB layers, and dimensions for both devices.
2026-06-06 Fix formatting in README.md for USB OUT section
2026-06-06 Fix formatting issues in README.md dimensions section
    Correct formatting and alignment of dimension details.
2026-06-07 Replace image in README with updated source
    Updated image source in README.md to a new URL.
2026-06-07 Add Onshape full assembly link to README
2026-06-07 Update Onshape assembly link in README

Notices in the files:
README.md:
License: OHL v2
